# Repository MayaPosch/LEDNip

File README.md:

# LED'Nip #

 LED'Nip is a 5-channel Cortex-M4-based LED controller and general STM32 development board. It has the following features:

- STM32F427 microcontroller (Cortex-M4, 180 MHz).
- 100 MBit Ethernet (LAN8472A).
- CAN (RJ-45 jacks).
- Three 12V channels for RGB LED strips or similar.
- Two channels for ~25 Watt LED panels each (5.5/2.1 mm jack) with constant current regulator (1A LDD-1000H or equivalent per channel).
- 24 VDC board supply voltage.
- SPI, I2C, U(S)ART, I2S and JTAG broken out into JST PH headers.

## Status ##

The LED'Nip hardware has been mostly validated. Test firmware can be found in its folder, with the firmware and backend service that will allow for the board to be used with building lighting and similar still under development.

## Project page

A project & product page can be found at: [http://www.nyantronics.com/lednip.php](http://www.nyantronics.com/lednip.php "LED'Nip")

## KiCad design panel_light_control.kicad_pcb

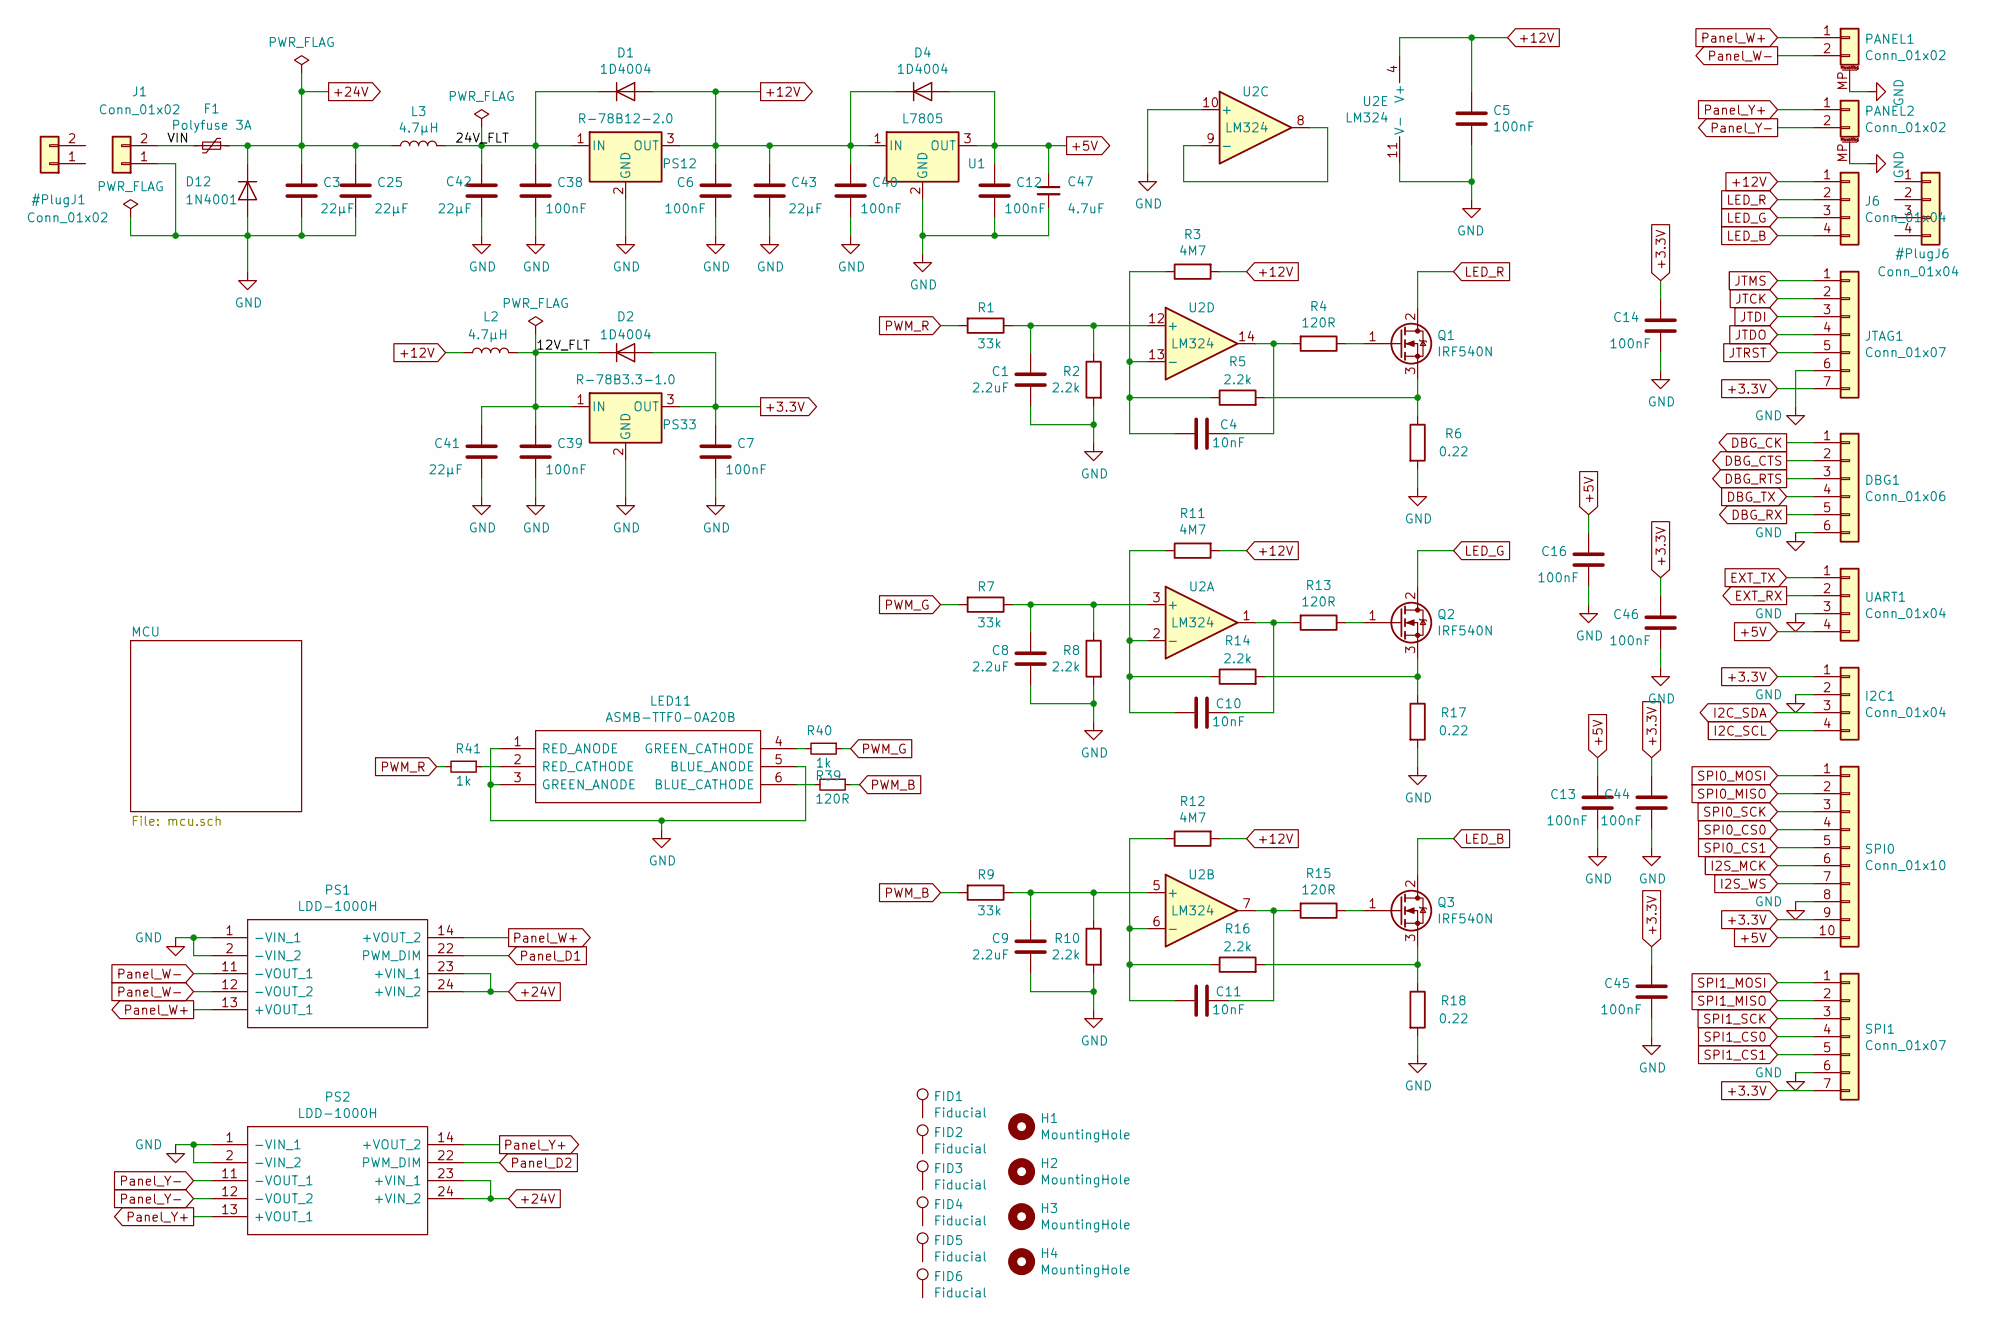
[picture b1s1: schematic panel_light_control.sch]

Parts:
C1, C8, C9: 2.2uF; C_0603_1608Metric; MPN C0603C225K9RACTU; Mouser 80-C0603C225K9R
C3, C25, C41, C42, C43: 22µF; C_1210_3225Metric; MPN GMK325BJ226MM-P; Mouser 963-GMK325BJ226MM-P
C4, C10, C11: 10nF; C_0603_1608Metric; MPN C0603C103K1REAUTO; Mouser 80-C0603C103K1REAUTO
C5, C6, C7, C12, C13, C14, C16, C38, C39, C40, C44, C45, C46: 100nF; C_0603_1608Metric; MPN C0603C104K5RECAUTO; Mouser 80-C0603C104K5REAUTO
C47: 4.7uF; C_0805_2012Metric; MPN GRM21BR71A475KE51L; Mouser 81-GRM21BR71A475KE1L
D1, D2, D4: 1D4004; D_SMA; MPN CGRA4004-G; Mouser 750-CGRA4004-G
D12: 1N4001; D_DO-41_SOD81_P3.81mm_Vertical_AnodeUp; MPN 1N4004-T; Mouser 621-1N4004
DBG1: Conn_01x06; JST_PH_S6B-PH-K_1x06_P2.00mm_Horizontal; MPN S6B-PH-K-S(LF)(SN)‎; DigiKey 455-1723-ND‎
F1: Polyfuse 3A; 30R400UF; MPN 30R300UU; Mouser 576-30R300UU
FID1, FID2, FID3, FID4, FID5, FID6: Fiducial; Fiducial_1mm_Dia_2.54mm_Outer_CopperTop
H1, H2, H3, H4: MountingHole; MountingHole_3.2mm_M3_DIN965
I2C1: Conn_01x04; JST_PH_S4B-PH-K_1x04_P2.00mm_Horizontal; MPN S4B-PH-K-S(LF)(SN)‎; DigiKey 455-1721-ND‎
J1: Conn_01x02; TerminalBlock_Phoenix_MKDS-1,5-2_1x02_P5.00mm_Horizontal; MPN 31320102; Mouser 571-796644-2
J6: Conn_01x04; TerminalBlock_Phoenix_MKDS-1,5-4_1x04_P5.00mm_Horizontal; MPN 31320104
JTAG1: Conn_01x07; JST_PH_S7B-PH-K_1x07_P2.00mm_Horizontal; MPN S7B-PH-K-S(LF)(SN)‎; DigiKey 455-1724-ND‎
L2, L3: 4.7µH; L_Taiyo-Yuden_NR-50xx; MPN VLS5045EX-4R7M-CA; Mouser 810-VLS5045EX4R7MCA
LED11: ASMB-TTF0-0A20B; ASMBTTF00A20B; Manufacturer_Part_Number ASMB-TTF0-0A20B; Mouser Part Number 630-ASMB-TTF0-0A20B
PANEL1, PANEL2: Conn_01x02; BarrelJack_CUI_PJ-063AH_Horizontal; MPN PJ-063AH; Mouser 490-PJ-063AH
PS1, PS2: LDD-1000H; LDD-700H; Manufacturer_Part_Number LDD-1000H; Mouser 709-LDD-1000H
PS12: R-78B12-2.0; Converter_DCDC_RECOM_R-78B-2.0_THT; Manufacturer_Part_Number R-78B12-2.0; Mouser 919-R-78B12-2.0
PS33: R-78B3.3-1.0; Converter_DCDC_RECOM_R-78B-2.0_THT; MPN R-78B3.3-1.0; Mouser 919-R-78B3.3-1.0
Q1, Q2, Q3: IRF540N; TO-220-3_Vertical; MPN IRF540NPBF; Mouser 942-IRF540NPBF
R1, R7, R9: 33k; R_0603_1608Metric; MPN RC0603FR-0733KL; Mouser 603-RC0603FR-0733KL
R2, R5, R8, R10, R14, R16: 2.2k; R_0603_1608Metric; MPN RC0603FR-072K2L; Mouser 603-RC0603FR-072K2L
R3, R11, R12: 4M7; R_0603_1608Metric; MPN RC0603FR-074M7L; Mouser 603-RC0603FR-074M7L
R4, R13, R15, R39: 120R; R_0603_1608Metric; MPN RC0603FR-07120RL; Mouser 603-RC0603FR-07120RL
R6, R17, R18: 0.22; R_1206_3216Metric; MPN KRL1632E-M-R220-F-T5; Mouser 754-KRL1632EMR220FT5
R40, R41: 1k; R_0603_1608Metric; MPN RC0603FR-071KL; Mouser 603-RC0603FR-071KL
SPI0: Conn_01x10; JST_PH_S10B-PH-K_1x10_P2.00mm_Horizontal; MPN S10B-PH-K-S(LF)(SN)‎; DigiKey 455-1727-ND‎
SPI1: Conn_01x07; JST_PH_S7B-PH-K_1x07_P2.00mm_Horizontal; MPN S7B-PH-K-S(LF)(SN); DigiKey 455-1724-ND‎
U1: L7805; TO-220-3_Vertical; MPN L7805CV; Mouser 511-L7805CV
U2: LM324; SOIC-14_3.9x8.7mm_P1.27mm; MPN LM324ADR; Mouser 595-LM324ADR
UART1: Conn_01x04; JST_PH_S4B-PH-K_1x04_P2.00mm_Horizontal; MPN S4B-PH-K-S(LF)(SN)‎; DigiKey 455-1721-ND‎

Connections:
+3.3V: C7.1, C14.1, C44.1, C45.1, C46.1, D2.2 (A), I2C1.1, JTAG1.7, PS33.3 (OUT), SPI0.9, SPI1.7; also elsewhere on the board
+5V: C12.1, C13.1, C16.1, C47.1, D4.2 (A), SPI0.10, U1.3 (OUT), UART1.4; also elsewhere on the board
+12V: C5.2, C6.1, C40.1, C43.1, D1.2 (A), D4.1 (K), J6.1, L2.1, PS12.3 (OUT), R3.2, R11.2, R12.2, U1.1 (IN), U2.4 (V+)
+24V: C3.1, C25.1, D12.1 (K), F1.1, L3.1, PS1.23 (+VIN_1), PS1.24 (+VIN_2), PS2.23 (+VIN_1), PS2.24 (+VIN_2)
/12V_FLT: C39.1, C41.1, D2.1 (K), L2.2, PS33.1 (IN)
/24V_FLT: C38.1, C42.1, D1.1 (K), L3.2, PS12.1 (IN)
/VIN: F1.2, J1.2
DBG_CK: DBG1.1; also elsewhere on the board
DBG_CTS: DBG1.2; also elsewhere on the board
DBG_RTS: DBG1.3; also elsewhere on the board
DBG_RX: DBG1.5; also elsewhere on the board
DBG_TX: DBG1.4; also elsewhere on the board
EXT_RX: UART1.2; also elsewhere on the board
EXT_TX: UART1.1; also elsewhere on the board
GND: C1.1, C3.2, C5.1, C6.2, C7.2, C8.1, C9.1, C12.2, C13.2, C14.2, C16.2, C25.2, C38.2, C39.2, C40.2, C41.2, C42.2, C43.2, C44.2, C45.2, C46.2, C47.2, D12.2 (A), DBG1.6, I2C1.2, J1.1, JTAG1.6, LED11.1 (RED_ANODE), LED11.3 (GREEN_ANODE), LED11.5 (BLUE_ANODE), PANEL1.MP (MountPin), PANEL2.MP (MountPin), PS1.1 (-VIN_1), PS1.2 (-VIN_2), PS2.1 (-VIN_1), PS2.2 (-VIN_2), PS12.2 (GND), PS33.2 (GND), R2.2, R6.2, R8.2, R10.2, R17.2, R18.2, SPI0.8, SPI1.6, U1.2 (GND), U2.10 (+), U2.11 (V-), UART1.3; also elsewhere on the board
I2C_SCL: I2C1.4; also elsewhere on the board
I2C_SDA: I2C1.3; also elsewhere on the board
I2S_MCK: SPI0.6; also elsewhere on the board
I2S_WS: SPI0.7; also elsewhere on the board
JTCK: JTAG1.2; also elsewhere on the board
JTDI: JTAG1.3; also elsewhere on the board
JTDO: JTAG1.4; also elsewhere on the board
JTMS: JTAG1.1; also elsewhere on the board
JTRST: JTAG1.5; also elsewhere on the board
LED_B: J6.4, Q3.2 (D)
LED_G: J6.3, Q2.2 (D)
LED_R: J6.2, Q1.2 (D)
unnamed: C1.2, R1.1, R2.1, U2.12 (+)
unnamed: C4.1, R4.2, U2.14
unnamed: C4.2, R3.1, R5.1, U2.13 (-)
unnamed: C8.2, R7.1, R8.1, U2.3 (+)
unnamed: C9.2, R9.1, R10.1, U2.5 (+)
unnamed: C10.1, R13.2, U2.1
unnamed: C10.2, R11.1, R14.1, U2.2 (-)
unnamed: C11.1, R15.2, U2.7
unnamed: C11.2, R12.1, R16.1, U2.6 (-)
unnamed: LED11.2 (RED_CATHODE), R41.1
unnamed: LED11.4 (GREEN_CATHODE), R40.2
unnamed: LED11.6 (BLUE_CATHODE), R39.2
unnamed: Q1.1 (G), R4.1
unnamed: Q1.3 (S), R5.2, R6.1
unnamed: Q2.1 (G), R13.1
unnamed: Q2.3 (S), R14.2, R17.1
unnamed: Q3.1 (G), R15.1
unnamed: Q3.3 (S), R16.2, R18.1
unnamed: U2.8, U2.9 (-)
PWM_B: R9.2, R39.1; also elsewhere on the board
PWM_G: R7.2, R40.1; also elsewhere on the board
PWM_R: R1.2, R41.2; also elsewhere on the board
Panel_D1: PS1.22 (PWM_DIM); also elsewhere on the board
Panel_D2: PS2.22 (PWM_DIM); also elsewhere on the board
Panel_W+: PANEL1.1, PS1.13 (+VOUT_1), PS1.14 (+VOUT_2)
Panel_W-: PANEL1.2, PS1.11 (-VOUT_1), PS1.12 (-VOUT_2)
Panel_Y+: PANEL2.1, PS2.13 (+VOUT_1), PS2.14 (+VOUT_2)
Panel_Y-: PANEL2.2, PS2.11 (-VOUT_1), PS2.12 (-VOUT_2)
SPI0_CS0: SPI0.4; also elsewhere on the board
SPI0_CS1: SPI0.5; also elsewhere on the board
SPI0_MISO: SPI0.2; also elsewhere on the board
SPI0_MOSI: SPI0.1; also elsewhere on the board
SPI0_SCK: SPI0.3; also elsewhere on the board
SPI1_CS0: SPI1.4; also elsewhere on the board
SPI1_CS1: SPI1.5; also elsewhere on the board
SPI1_MISO: SPI1.2; also elsewhere on the board
SPI1_MOSI: SPI1.1; also elsewhere on the board
SPI1_SCK: SPI1.3; also elsewhere on the board

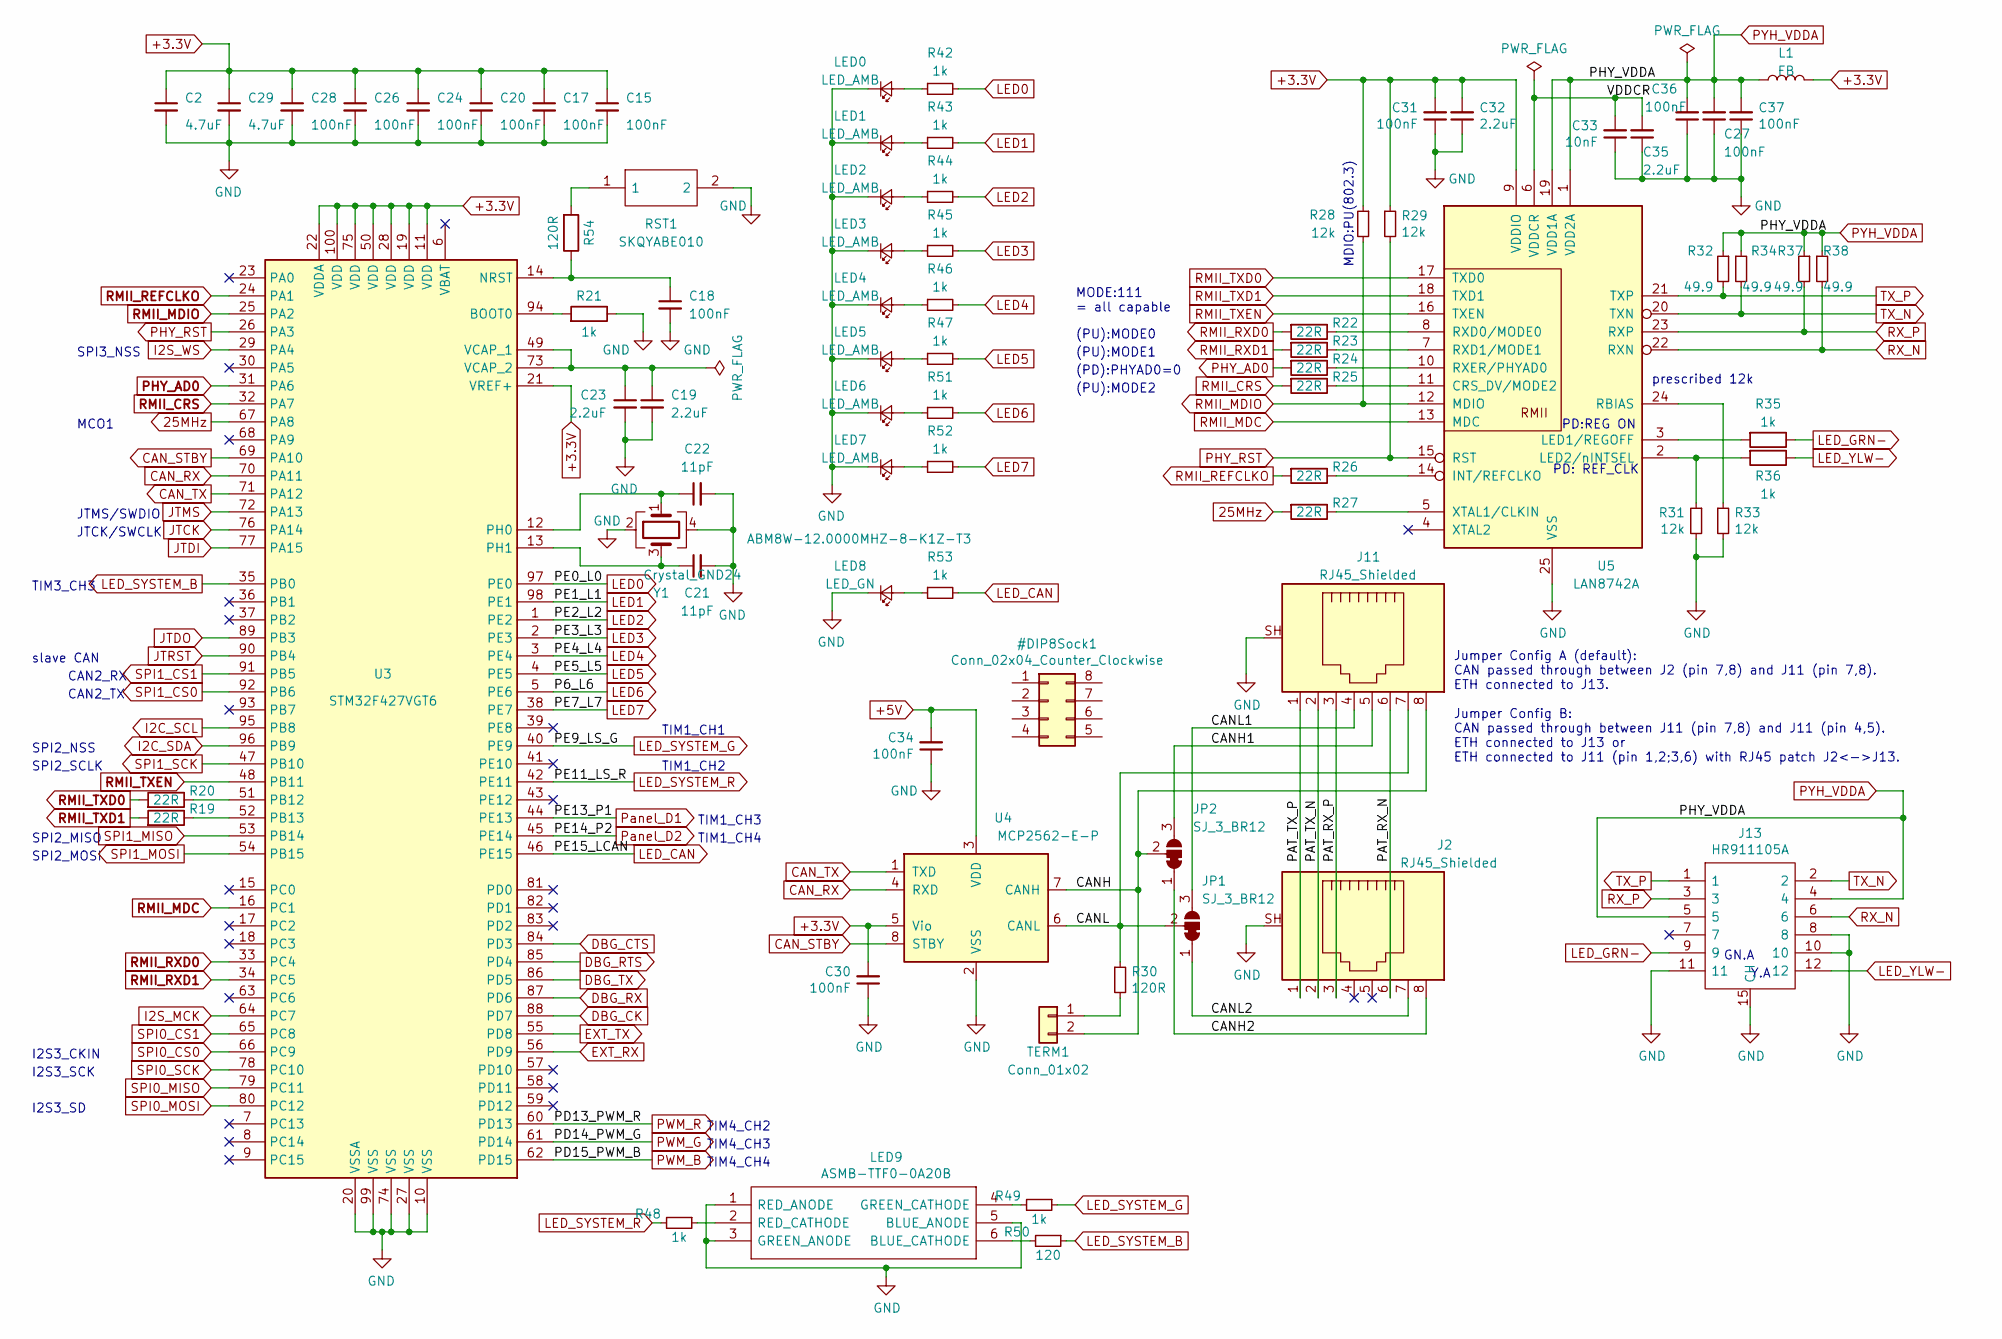
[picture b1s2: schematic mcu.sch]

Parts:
C2, C29: 4.7uF; C_0805_2012Metric; MPN GRM21BR71A475KE51L; Mouser 81-GRM21BR71A475KE1L
C15, C17, C18, C20, C24, C26, C27, C28, C30, C31, C34, C36, C37: 100nF; C_0603_1608Metric; MPN C0603C104K5RECAUTO; Mouser 80-C0603C104K5REAUTO
C19, C23, C32, C35: 2.2uF; C_0603_1608Metric; MPN C0603C225K9RACTU; Mouser 80-C0603C225K9R
C21, C22: 11pF; C_0603_1608Metric; MPN CBR06C110F5GAC; Mouser 80-CBR06C110F5G
C33: 10nF; C_0603_1608Metric; MPN C0603C103K1REAUTO; Mouser 80-C0603C103K1REAUTO
J2, J11: RJ45_Shielded; RJ45_Amphenol_RJHSE5380; MPN RJHSE-5380; Mouser 523-RJHSE-5380
J13: HR911105A; HR911105A_1; Manufacturer_Part_Number HR911105A; Mouser 710-7499011121A (WE near match)
JP1, JP2: SJ_3_BR12; SolderJumper-3_P1.3mm_Bridged12_RoundedPad1.0x1.5mm
L1: FB; L_0603_1608Metric; MPN BLM18KG121TN1D; Mouser 81-BLM18KG121TN1D
LED0, LED1, LED2, LED3, LED4, LED5, LED6, LED7: LED_AMB; LED_0603_1608Metric_Castellated; MPN LTST-C190AKT; Mouser 859-LTST-C190AKT
LED8: LED_GN; LED_0603_1608Metric_Castellated; MPN LTST-C190KGKT; Mouser 859-LTST-C190KGKT
LED9: ASMB-TTF0-0A20B; ASMBTTF00A20B; Manufacturer_Part_Number ASMB-TTF0-0A20B; Mouser Part Number 630-ASMB-TTF0-0A20B
R19, R20, R22, R23, R24, R25, R26, R27: 22R; R_0603_1608Metric; MPN RC0603JR-0722RL; Mouser 603-RC0603JR-0722RL
R21, R35, R36, R42, R43, R44, R45, R46, R47, R49, R51, R52, R53: 1k; R_0603_1608Metric; MPN RC0603FR-071KL; Mouser 603-RC0603FR-071KL
R28, R29, R31, R33: 12k; R_0603_1608Metric; MPN RC0603FR-0712KL; Mouser 603-RC0603FR-0712KL
R30, R54: 120R; R_0603_1608Metric; MPN RC0603FR-07120RL; Mouser 603-RC0603FR-07120RL
R32, R34, R37, R38: 49.9; R_0603_1608Metric; MPN RC0603FR-0749R9L; Mouser 603-RC0603FR-0749R9L
R48: 1k; R_0603_1608Metric; MPN RC0603FR-07120RL; Mouser 603-RC0603FR-07120RL
R50: 120; R_0603_1608Metric; MPN RC0603FR-071KL; Mouser 603-RC0603FR-071KL
RST1: SKQYABE010; Manufacturer_Part_Number SKQYABE010; Mouser 688-SKQYAB
TERM1: Conn_01x02; PinHeader_1x02_P2.54mm_Vertical; MPN S2B-PH-K-S(LF)(SN)‎; DigiKey 455-1719-ND
U3: STM32F427VGT6; LQFP-100_14x14mm_P0.5mm; MPN STM32F427VGT6; Mouser 511-STM32F427VGT6
U4: MCP2562-E-P; DIP-8_W7.62mm_Socket; MPN MCP2562-E/P; Mouser 579-MCP2562-E/P
U5: LAN8742A; QFN-24-1EP_4x4mm_P0.5mm_EP2.6x2.6mm; MPN LAN8742A-CZ-TR; Mouser 579-LAN8742A-CZ-TR
Y1: Crystal_GND24; Crystal_SMD_Abracon_ABM8G-4Pin_3.2x2.5mm; MPN ABM8W-12.0000MHZ-8-K1Z-T3; Mouser 815-8W12-8K1ZT

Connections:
25MHz: R27.2, U3.67 (PA8)
+3.3V: C2.1, C15.1, C17.1, C20.1, C24.1, C26.1, C28.1, C29.1, C30.2, C31.2, C32.2, L1.2, R28.1, R29.1, U3.11 (VDD), U3.19 (VDD), U3.21 (VREF+), U3.22 (VDDA), U3.28 (VDD), U3.50 (VDD), U3.75 (VDD), U3.100 (VDD), U4.5 (Vio), U5.9 (VDDIO); also elsewhere on the board
+5V: C34.2, U4.3 (VDD); also elsewhere on the board
/MCU/CANH: J11.8, JP2.2 (C), TERM1.2, U4.7 (CANH)
/MCU/CANH1: J11.5, JP2.3 (B)
/MCU/CANH2: J2.8, JP2.1 (A)
/MCU/CANL: J11.7, JP1.2 (C), R30.1, U4.6 (CANL)
/MCU/CANL1: J11.4, JP1.3 (B)
/MCU/CANL2: J2.7, JP1.1 (A)
/MCU/PAT_RX_N: J2.6, J11.6
/MCU/PAT_RX_P: J2.3, J11.3
/MCU/PAT_TX_N: J2.2, J11.2
/MCU/PAT_TX_P: J2.1, J11.1
/MCU/VDDCR: C33.2, C35.2, U5.6 (VDDCR)
CAN_RX: U3.70 (PA11), U4.4 (RXD)
CAN_STBY: U3.69 (PA10), U4.8 (STBY)
CAN_TX: U3.71 (PA12), U4.1 (TXD)
DBG_CK: U3.88 (PD7); also elsewhere on the board
DBG_CTS: U3.84 (PD3); also elsewhere on the board
DBG_RTS: U3.85 (PD4); also elsewhere on the board
DBG_RX: U3.87 (PD6); also elsewhere on the board
DBG_TX: U3.86 (PD5); also elsewhere on the board
EXT_RX: U3.56 (PD9); also elsewhere on the board
EXT_TX: U3.55 (PD8); also elsewhere on the board
GND: C2.2, C15.2, C17.2, C18.2, C19.2, C20.2, C21.2, C22.2, C23.2, C24.2, C26.2, C27.1, C28.2, C29.2, C30.1, C31.1, C32.1, C33.1, C34.1, C35.1, C36.1, C37.1, J2.SH, J11.SH, J13.8, J13.10, J13.11, J13.15 (CH), J13.16 (CH), LED0.1 (K), LED1.1 (K), LED2.1 (K), LED3.1 (K), LED4.1 (K), LED5.1 (K), LED6.1 (K), LED7.1 (K), LED8.1 (K), LED9.1 (RED_ANODE), LED9.3 (GREEN_ANODE), LED9.5 (BLUE_ANODE), R21.1, R31.2, R33.2, RST1.2, U3.10 (VSS), U3.20 (VSSA), U3.27 (VSS), U3.74 (VSS), U3.99 (VSS), U4.2 (VSS), U5.25 (VSS), Y1.2, Y1.4; also elsewhere on the board
I2C_SCL: U3.95 (PB8); also elsewhere on the board
I2C_SDA: U3.96 (PB9); also elsewhere on the board
I2S_MCK: U3.64 (PC7); also elsewhere on the board
I2S_WS: U3.29 (PA4); also elsewhere on the board
JTCK: U3.76 (PA14); also elsewhere on the board
JTDI: U3.77 (PA15); also elsewhere on the board
JTDO: U3.89 (PB3); also elsewhere on the board
JTMS: U3.72 (PA13); also elsewhere on the board
JTRST: U3.90 (PB4); also elsewhere on the board
LED0: R42.2, U3.97 (PE0)
LED1: R43.2, U3.98 (PE1)
LED2: R44.2, U3.1 (PE2)
LED3: R45.2, U3.2 (PE3)
LED4: R46.2, U3.3 (PE4)
LED5: R47.2, U3.4 (PE5)
LED6: R51.2, U3.5 (PE6)
LED7: R52.2, U3.38 (PE7)
LED_CAN: R53.2, U3.46 (PE15)
LED_GRN-: J13.9, R35.1
LED_SYSTEM_B: R50.1, U3.35 (PB0)
LED_SYSTEM_G: R49.1, U3.40 (PE9)
LED_SYSTEM_R: R48.2, U3.42 (PE11)
LED_YLW-: J13.12, R36.1
unnamed: C18.1, R54.1, U3.14 (NRST)
unnamed: C19.1, C23.1, U3.49 (VCAP_1), U3.73 (VCAP_2)
unnamed: C21.1, U3.13 (PH1), Y1.3
unnamed: C22.1, U3.12 (PH0), Y1.1
unnamed: LED0.2 (A), R42.1
unnamed: LED1.2 (A), R43.1
unnamed: LED2.2 (A), R44.1
unnamed: LED3.2 (A), R45.1
unnamed: LED4.2 (A), R46.1
unnamed: LED5.2 (A), R47.1
unnamed: LED6.2 (A), R51.1
unnamed: LED7.2 (A), R52.1
unnamed: LED8.2 (A), R53.1
unnamed: LED9.2 (RED_CATHODE), R48.1
unnamed: LED9.4 (GREEN_CATHODE), R49.2
unnamed: LED9.6 (BLUE_CATHODE), R50.2
unnamed: R19.1, U3.52 (PB13)
unnamed: R20.1, U3.51 (PB12)
unnamed: R21.2, U3.94 (BOOT0)
unnamed: R22.1, U5.8 (RXD0/MODE0)
unnamed: R23.1, U5.7 (RXD1/MODE1)
unnamed: R24.1, U5.10 (RXER/PHYAD0)
unnamed: R25.1, U5.11 (CRS_DV/MODE2)
unnamed: R26.1, U5.14 (INT/REFCLKO)
unnamed: R27.1, U5.5 (XTAL1/CLKIN)
unnamed: R30.2, TERM1.1
unnamed: R31.1, R36.2, U5.2 (LED2/nINTSEL)
unnamed: R33.1, U5.24 (RBIAS)
unnamed: R35.2, U5.3 (LED1/REGOFF)
unnamed: R54.2, RST1.1
PHY_AD0: R24.2, U3.31 (PA6)
PHY_RST: R29.2, U3.26 (PA3), U5.15 (RST)
PWM_B: U3.62 (PD15); also elsewhere on the board
PWM_G: U3.61 (PD14); also elsewhere on the board
PWM_R: U3.60 (PD13); also elsewhere on the board
PYH_VDDA: C27.2, C36.2, C37.2, J13.4, J13.5, L1.1, R32.1, R34.1, R37.1, R38.1, U5.1 (VDD2A), U5.19 (VDD1A)
Panel_D1: U3.44 (PE13); also elsewhere on the board
Panel_D2: U3.45 (PE14); also elsewhere on the board
RMII_CRS: R25.2, U3.32 (PA7)
RMII_MDC: U3.16 (PC1), U5.13 (MDC)
RMII_MDIO: R28.2, U3.25 (PA2), U5.12 (MDIO)
RMII_REFCLKO: R26.2, U3.24 (PA1)
RMII_RXD0: R22.2, U3.33 (PC4)
RMII_RXD1: R23.2, U3.34 (PC5)
RMII_TXD0: R20.2, U5.17 (TXD0)
RMII_TXD1: R19.2, U5.18 (TXD1)
RMII_TXEN: U3.48 (PB11), U5.16 (TXEN)
RX_N: J13.6, R38.2, U5.22 (RXN)
RX_P: J13.3, R37.2, U5.23 (RXP)
SPI0_CS0: U3.66 (PC9); also elsewhere on the board
SPI0_CS1: U3.65 (PC8); also elsewhere on the board
SPI0_MISO: U3.79 (PC11); also elsewhere on the board
SPI0_MOSI: U3.80 (PC12); also elsewhere on the board
SPI0_SCK: U3.78 (PC10); also elsewhere on the board
SPI1_CS0: U3.92 (PB6); also elsewhere on the board
SPI1_CS1: U3.91 (PB5); also elsewhere on the board
SPI1_MISO: U3.53 (PB14); also elsewhere on the board
SPI1_MOSI: U3.54 (PB15); also elsewhere on the board
SPI1_SCK: U3.47 (PB10); also elsewhere on the board
TX_N: J13.2, R34.2, U5.20 (TXN)
TX_P: J13.1, R32.2, U5.21 (TXP)

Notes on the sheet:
MCO1
prescribed 12k
PD:REG ON
PD: REF_CLK
MDIO:PU(802.3)
(PU):MODE0
(PU):MODE1
(PU):MODE2
(PD):PHYAD0=0
MODE:111 = all capable
GN.A
Y.A
JTMS/SWDIO
JTCK/SWCLK
CAN2_RX
CAN2_TX
slave CAN
I2S3_SD
I2S3_SCK
I2S3_CKIN
SPI3_NSS
SPI2_SCLK
SPI2_MOSI
SPI2_MISO
SPI2_NSS
TIM1_CH3
TIM1_CH4
TIM4_CH2
TIM4_CH3
TIM4_CH4
TIM3_CH3
TIM1_CH1
TIM1_CH2
Jumper Config A (default): CAN passed through between J2 (pin 7,8) and J11 (pin 7,8). ETH connected to J13. Jumper Config B: CAN passed through between J11 (pin 7,8) and J11 (pin 4,5). ETH connected to J13 or ETH connected to J11 (pin 1,2;3,6) with RJ45 patch J2<->J13.

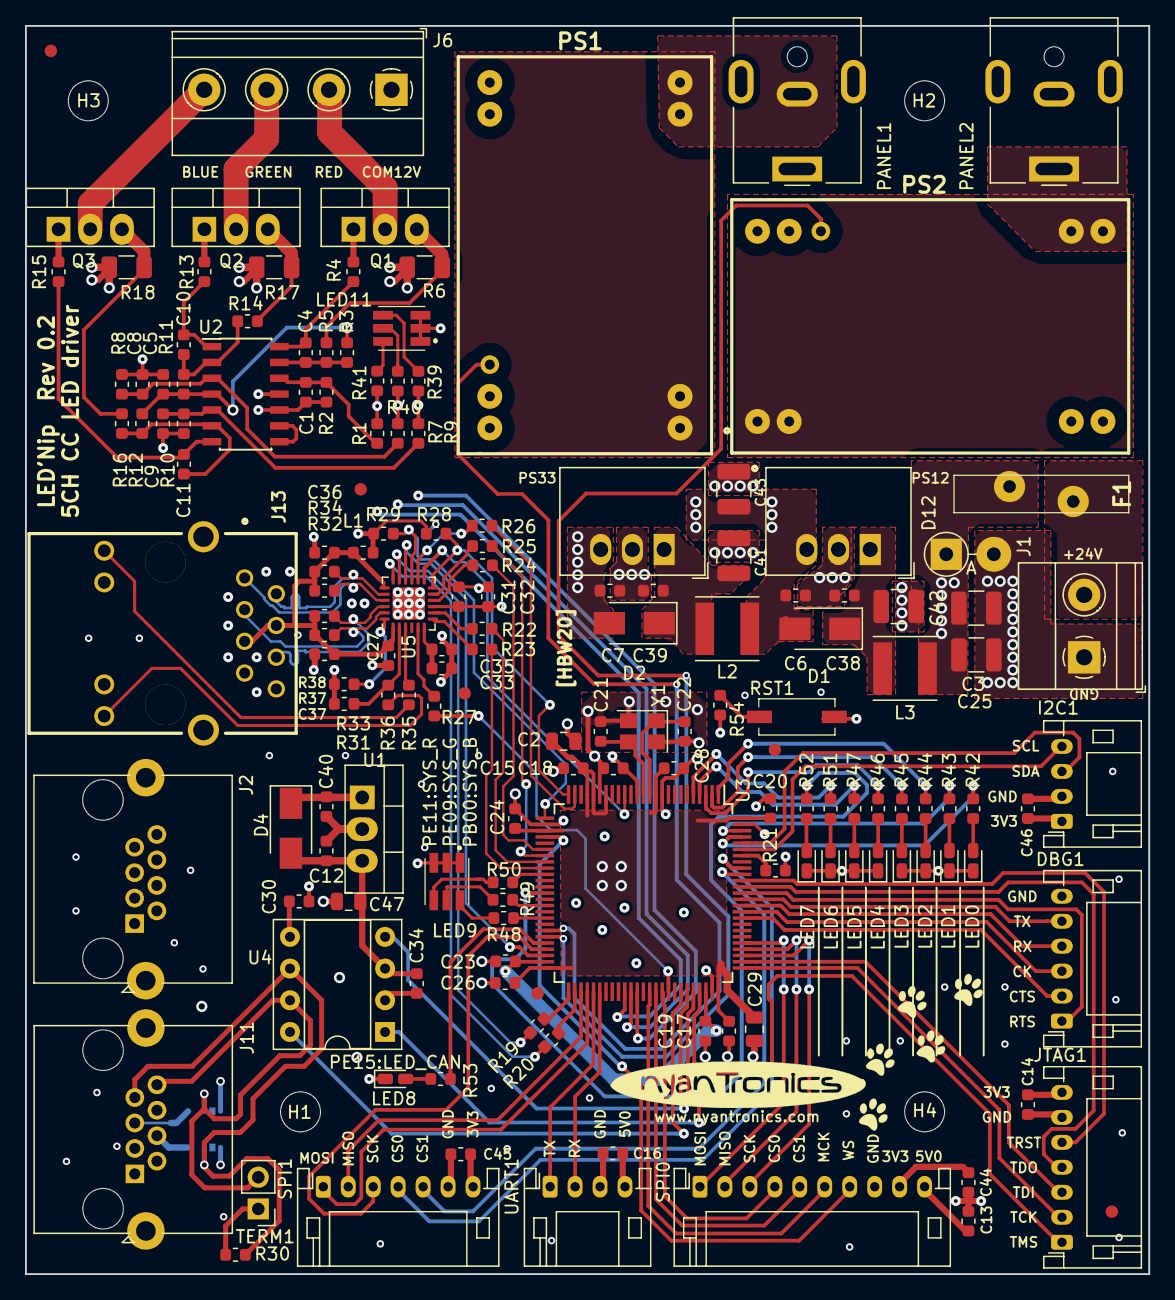
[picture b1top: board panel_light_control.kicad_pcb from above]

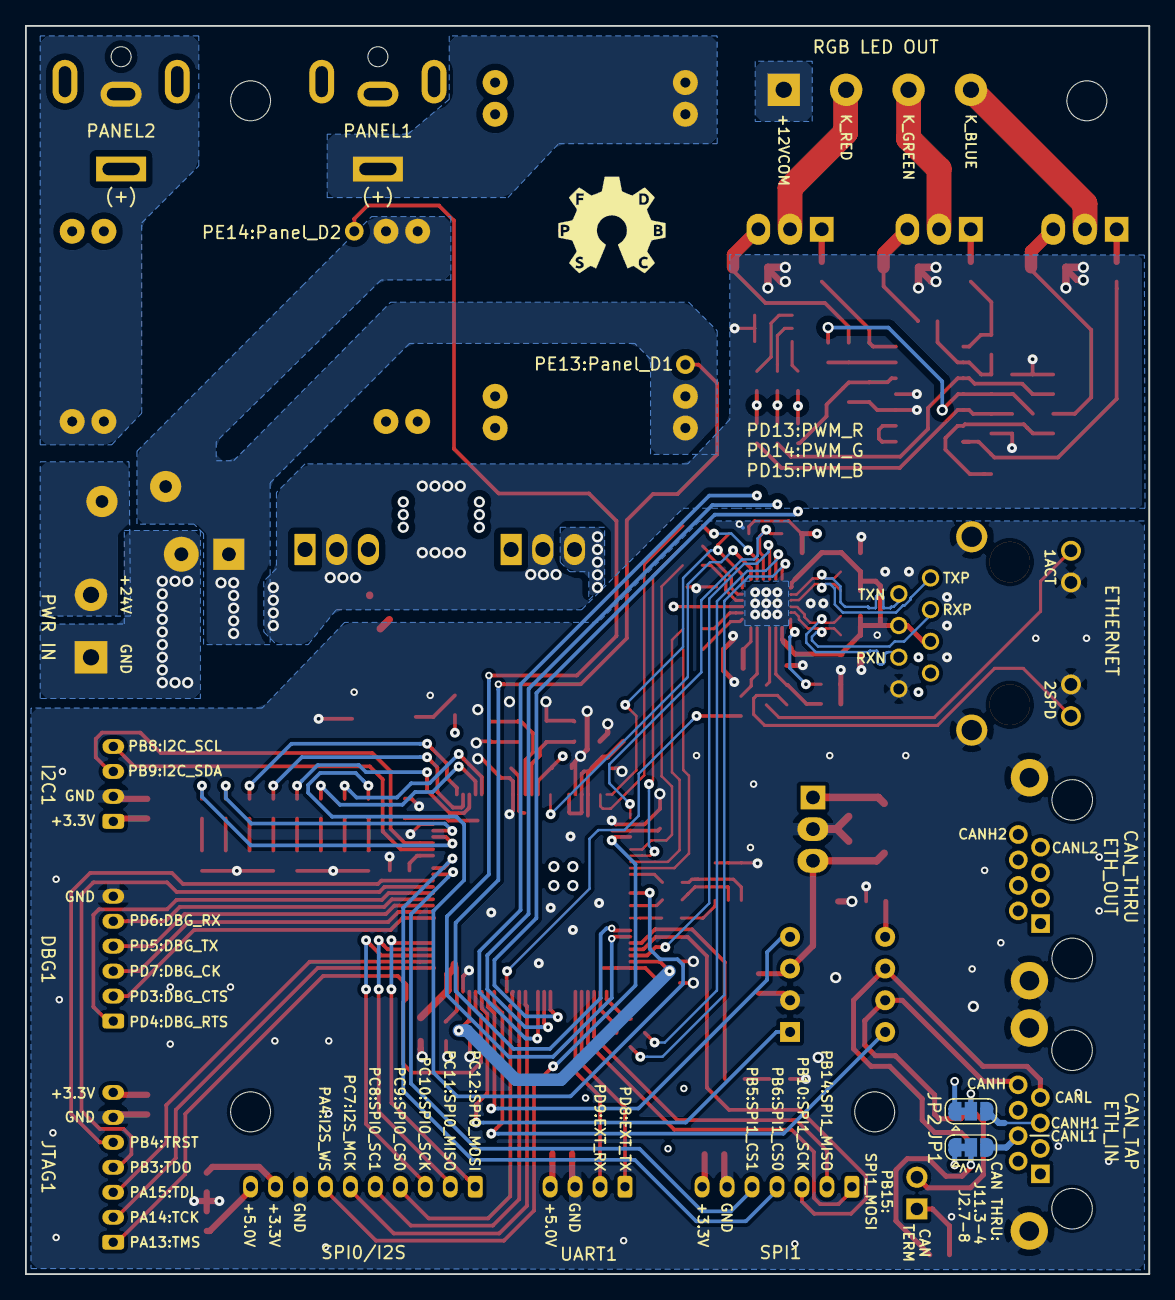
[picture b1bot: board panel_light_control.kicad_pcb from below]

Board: 4 copper layers, 90.0 x 100.0 mm, 160 parts (2 on the bottom side), 140 nets.

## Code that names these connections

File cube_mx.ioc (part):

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Mcu.Name=STM32F207V(C-E-F-G)Tx
Mcu.Package=LQFP100
Mcu.UserName=STM32F207VGTx
PA1.Mode=RMII
PA1.Signal=ETH_REF_CLK
PA10.GPIOParameters=GPIO_Label
PA10.GPIO_Label=CAN_STBY
PA10.Signal=GPIO_Output
PA11.Mode=Master
PA11.Signal=CAN1_RX
PA12.Mode=Master
PA12.Signal=CAN1_TX
PA13.Mode=JTAG_5_pins
PA13.Signal=SYS_JTMS-SWDIO
PA14.Mode=JTAG_5_pins
PA14.Signal=SYS_JTCK-SWCLK
PA15.Mode=JTAG_5_pins
PA15.Signal=SYS_JTDI
PA2.Mode=RMII
PA2.Signal=ETH_MDIO
PA3.GPIOParameters=GPIO_Label
PA3.GPIO_Label=PHY_RST
PA3.Signal=GPIO_Output
PA4.Mode=NSS_Signal_Hard_Output
PA4.Signal=SPI3_NSS
PA6.GPIOParameters=GPIO_Label
PA6.GPIO_Label=PHY_AD0
PA6.Signal=GPIO_Output
PA7.Mode=RMII
PA7.Signal=ETH_CRS_DV
PA8.Mode=Clock-out-1
PA8.Signal=RCC_MCO_1
PB0.GPIOParameters=GPIO_Label
PB0.GPIO_Label=LED_SYSTEM_B
PB0.Signal=S_TIM3_CH3
PB10.Mode=Full_Duplex_Master
PB10.Signal=SPI2_SCK
PB11.Mode=RMII
PB11.Signal=ETH_TX_EN
PB12.Mode=RMII
PB12.Signal=ETH_TXD0
PB13.Mode=RMII
PB13.Signal=ETH_TXD1
PB14.Mode=Full_Duplex_Master
PB14.Signal=SPI2_MISO
PB15.Mode=Full_Duplex_Master
PB15.Signal=SPI2_MOSI
PB3.Mode=JTAG_5_pins
PB3.Signal=SYS_JTDO-SWO
PB4.Mode=JTAG_5_pins
PB4.Signal=SYS_JTRST
PB5.GPIOParameters=GPIO_Label
PB5.GPIO_Label=SPI2_CS1
PB5.Signal=GPIO_Output
PB6.GPIOParameters=GPIO_Label
PB6.GPIO_Label=SPI2_CS0
PB6.Signal=GPIO_Output
PB8.Mode=I2C
PB8.Signal=I2C1_SCL
PB9.Mode=I2C
PB9.Signal=I2C1_SDA
PC1.Mode=RMII
PC1.Signal=ETH_MDC
PC10.Mode=Full_Duplex_Master
PC10.Signal=SPI3_SCK
PC11.Mode=Full_Duplex_Master
PC11.Signal=SPI3_MISO
PC12.Mode=Full_Duplex_Master
PC12.Signal=SPI3_MOSI
PC4.Mode=RMII
PC4.Signal=ETH_RXD0
PC5.Mode=RMII
PC5.Signal=ETH_RXD1
PC8.GPIOParameters=GPIO_Label
PC8.GPIO_Label=SPI3_CS0
PC8.Signal=GPIO_Output
PC9.GPIOParameters=GPIO_Label
PC9.GPIO_Label=I2S_CKIN/CS1
PC9.Mode=Audio_ClockIn
PC9.Signal=I2S_CKIN
PD13.GPIOParameters=GPIO_Label
PD13.GPIO_Label=PWM_R
PD13.Signal=S_TIM4_CH2
PD14.GPIOParameters=GPIO_Label
PD14.GPIO_Label=PWM_G
PD14.Signal=S_TIM4_CH3
PD15.GPIOParameters=GPIO_Label
PD15.GPIO_Label=PWM_B
PD15.Signal=S_TIM4_CH4
PD3.Mode=CTS_RTS
PD3.Signal=USART2_CTS
PD4.Mode=CTS_RTS
PD4.Signal=USART2_RTS
PD5.Mode=Asynchronous
PD5.Signal=USART2_TX
PD6.Mode=Asynchronous
PD6.Signal=USART2_RX
PD8.Mode=Asynchronous
PD8.Signal=USART3_TX
PD9.Mode=Asynchronous
PD9.Signal=USART3_RX
PE0.GPIOParameters=GPIO_Label
PE0.GPIO_Label=LED0
PE0.Signal=GPIO_Output
PE1.GPIOParameters=GPIO_Label
PE1.GPIO_Label=LED1
PE1.Signal=GPIO_Output
PE11.GPIOParameters=GPIO_Label
PE11.GPIO_Label=LED_SYSTEM_R
PE11.Signal=S_TIM1_CH2
PE13.GPIOParameters=GPIO_Label
PE13.GPIO_Label=PANEL_D1
PE13.Signal=S_TIM1_CH3
PE14.GPIOParameters=GPIO_Label
PE14.GPIO_Label=PANEL_D2
PE14.Signal=S_TIM1_CH4
PE15.GPIOParameters=GPIO_Label
PE15.GPIO_Label=LED_CAN
PE15.Signal=GPIO_Output
PE2.GPIOParameters=GPIO_Label
PE2.GPIO_Label=LED2
PE2.Signal=GPIO_Output
PE3.GPIOParameters=GPIO_Label
PE3.GPIO_Label=LED3
PE3.Signal=GPIO_Output
PE4.GPIOParameters=GPIO_Label
PE4.GPIO_Label=LED4
PE4.Signal=GPIO_Output
PE5.GPIOParameters=GPIO_Label
PE5.GPIO_Label=LED5
PE5.Signal=GPIO_Output
PE6.GPIOParameters=GPIO_Label
PE6.GPIO_Label=LED6
PE6.Signal=GPIO_Output
PE7.GPIOParameters=GPIO_Label
PE7.GPIO_Label=LED7
PE7.Signal=GPIO_Output
PE9.GPIOParameters=GPIO_Label
PE9.GPIO_Label=LED_SYSTEM_G
PE9.Signal=S_TIM1_CH1
PH0-OSC_IN.Mode=HSE-External-Oscillator
PH0-OSC_IN.Signal=RCC_OSC_IN
PH1-OSC_OUT.Mode=HSE-External-Oscillator
PH1-OSC_OUT.Signal=RCC_OSC_OUT
RCC.HSE_VALUE=12000000
RCC.SYSCLKFreq_VALUE=100000000
RCC.SYSCLKSource=RCC_SYSCLKSOURCE_PLLCLK
board=custom

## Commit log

2018-10-14 Initial commit. Finish programming/debug interface.
2018-10-16 Finished initial schematic review.
2018-10-16 Tweak I2S breakout, generate netlist.
2018-10-17 Started layouting.
2018-10-17 Sorted passives on board.
2018-10-17 Finished initial layout LED CV, CAN.
2018-10-17 Finished basic board layout.
2018-10-18 Board layout tweaks.
2018-10-18 Tweaking power section layout.
2018-10-18 Finished initial PHY-magjack routing.
2018-10-20 adds PHY PU/PD config pin comments
2018-10-21 schematic clean-up, BOM info partially added
2018-10-21 PHY routing done? Current sink routing is back to square one (yay fwd annotations)
2018-10-21 further re-arrangement, PCB is now 100x90 mm² \o/. A bit more placement to do, then back to routing :>
2018-10-22 Tweaked LED sink layout, fixed 3D model for 1 RJ45 jack.
2018-10-22 Tweaked MOSFET sink layout. Changed LM324 to SOIC.
2018-10-22 Add LEDs, tweak MOSFET sink.
2018-10-22 3.3V buck converter now connected to 12V (prep for 48V>12V upgrade regarding IoP applicability)
2018-10-22 two sections left to place: 3ch current sink, microcontroller area. Todo: * find proper barrel jacks, spec MPN, Mouser * add status LEDs to the LDD-H outputs * add 7th LED for funsies :> * swap LM324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
2018-10-23 THT pad restring sizes increase for mechanical stability; generalized LED arrangement for more flexibility (8 bit display, CAN LED, PWM and general purpose RGB) and development-style look and feel; p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
2018-10-23 R-78B3.3 footprint fixed (had the E version -> mirrored), next: place remaining current sink circuit parts, route upper half of the PCB, tidy up CAN placement, verify µC pin mapping again, route lowe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
2018-10-27 RGB current sink placed and routed. All placement should be done now, next: check barrel jack footprint, do power routing, think about input protection for GPIOs, possibly add resistor arrays, route 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
2018-10-27 silkscreen clean-up
2018-10-27 PS1-> Panel1, PS2-> Panel2, PS12->12V, PS33-> 3.3V.
2018-10-27 missed silkscreen bits tidied up
2018-10-27 add CAN termination jumper, switch-mode DCDC power routing and current sink routing done. Barrel jacks still need swapping?
2018-10-27 change I2S connector footprint back from 11 pin to 10 pin (MCK, SCK, WS... missing something?). More silkscreen clean-up and a bit of routing.
2018-10-27 minor touch-ups. ToDo: think about barrel jacks, input protection, finish routing (RMII, 3.3V plane and traces, general purpose signals), then review.
2018-10-27 routing almost done. ToDo: fix symbols to include shielding on some connectors. finish routing. Add GND copper pour on bottom side.
2018-10-27 first pass routing done (0 air wires). ToDo: fix connector shielding.
2018-10-28 all connector shields are now connected to ground. Note HR911105A LED pins are offset by 4.9mm whereas the WE LED pins are at 4.1mm. Can still fit the WE part? but it won't be pretty.
2018-10-28 lots of labels!
2018-10-28 Removed redundant silkscreen labels.
2018-10-28 Changes to 3.3V polygon shape to remove overlap with 24V, 12V input section. Some improvements and corrections to the silkscreen. 7805 location checked for 78B05 clearance - will work in case 5V >100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
2018-10-28 Added board art.
2018-10-28 added BOM info, minor tweaks to artwork
2018-11-01 adds reset button, some xtal guarding. Schematic reviewed in this version, see https://hackmd.io/-iUjavK_Rz-11sfgLlTnuA# - xtal could be swapped for C_L 10 pF version to reduce susceptibility to envi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
2018-11-04 pinout validated against CubeMX listing (.ioc added), some nets renamed, system RGB LED reconnected. Reconnected I2C lines to include CAN alternate function. Warning: * bottom silkscreen labels might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
2018-11-05 swap xtal for 12 MHz type with CL=8pF -> 2MHz PLL in (optimum), larger load capacitors offering higher noise immunity, HSE gain margin should still be ok, silk screen changes due to secondary CAN int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
2018-11-05 Generated v0.1 Gerbers & Drill file.
2018-11-05 final touches: add fiducials for PCBA
2018-11-05 Update Gerbers & Drill files.
2018-11-06 add project flow diagram for the deployment of 25+ boards. Get draw.io: https://about.draw.io/integrations/#integrations_offline
2018-11-16 BOM DONE
2018-11-16 BOM completed, inventory checked and listed in BOM. Adds project diagram.
2018-11-25 PLCC-4 RGB LEDs LED9 and LED10 are the wrong parts (common cathode required, part is common anode and different input). Fix: source 0606 LEDs (metric 1616) - RD1616-63RGBC-C2CA or DL-PCB0606RGBC-C2. 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
2018-12-12 project moving forward (draw.io diagram updated), added test report (work in progress)
2019-01-01 Created an OpenOCD config file and documentation on it. Added quick protocol of the hardware power-up.
2019-01-01 Add auto-generated firmware. Modify Makefile to add 'flash' target.
2019-01-01 added -event reset-assert to define system reset (replacing srst), including documentation.
2019-01-02 .cfg comments updated
2019-01-02 channel 1 pins are called BDBUSn, names updated. Verified reset things (signal is called nTRST while the function is called trst... which is a bit odd but seems to be valid. The AIRCR write also seem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
2019-01-02 includes answers to the "-event reset-assert" usage question, adds flashing capability to the makefile. In essence, OpenOCD contains all reset functionality needed for an STM32F4 through config and b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
2019-01-04 Add initial code for interrupt routine for LED demo on TIM2
2019-01-06 Finish PWM curve for panel D1 pin for initial testing.
2019-01-06 Attempt to implement interrupt-based timer for PWM manipulation...
2019-01-06 Get basic dimming working on LED panel output D1.
2019-01-07 change PWM mode from TIM_COUNTERMODE_UP to TIM_COUNTERMODE_CENTERALIGNED1 and change TIM1 CH4 OCPolarity from TIM_OCPOLARITY_HIGH to TIM_OCPOLARITY_LOW to create 180° interleaved PWM within one TIM. 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
2019-01-07 modified init for TIM1, TIM3, TIM4 (up -> centeraligned1, same period, same prescaler). Dedicated update functions for the RGB and panel PWM groups. Runs on hardware but the PWM frequency needs to be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
2019-01-09 Enable basic PWM sweep on RGB LED channels.
2019-01-09 Add rough HSV-based colour sweep on the RGB PWM pins.
2019-01-09 Change PWM limit division factor for 70% max current on RGB outputs.
2019-01-09 Add brief linger at the ends of the RGB PWM sweep sequence.
2019-01-10 Tweak linger on HSV colour sweep begin and end points.
2019-01-10 introduces user constants PWM_TIMER_RELOAD,10000;PWM_TIMER_PRESCALER,12 and properly configures TIM1, TIM3 and TIM4 (all TIM_COUNTERMODE_CENTERALIGNED1, ITM1 ClockDivision set to TIM_CLOCKDIVISION_DI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
2019-01-11 attempt to sort code back into USER labelled sections to be compatible with CubeMX behaviour.
2019-01-12 Updated project according to .ioc file. Experimentation with RELOAD and PRESCALER to debug TIM4 "clock too slow" issue. APB1: 50MHz, APB2: 100MHz. RELOAD = 10000. PRESCALER = 9: 4 ms period, PRESCALE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
2019-01-13 played around with CK_IN prescalers for TIM1 and TIM3..4. APB1 and APB2 timer clocks are both 80 MHz now so TIM1, TIM3 and TIM4 behave consistently. +RCC.48MHZClocksFreq_Value=40000000 +RCC.AHBFreq_V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
2019-01-14 sets PHY_RST from push-pull low to open-drain high to release nRST, PHYAD0 is kept low -> 0x00 changed in CubeMX from 1 to 0. Change SPI CS pins from low to high speed GPIO. Current draw is higher an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
2019-03-10 restored MCO1 = 25 MHz, PHY blinking pattern changed (SPEED on permanently, ACT fast blinking, RMII-RXDn activity) but TXEN only stays high for 6µs max. No SMI activity within 100ms after that.
2019-03-12 restored clock setup (source was int. RC, now back to 12 MHz ext. xtal), MCO verified to be 25.000 MHz. Played around with lwip checksum generation. Also recommend looking at CubeMX stacked pin optio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
2019-03-13 add MX_LWIP_Process(); to main loop (non-interrupt-based polling mode for non-OS operation) ... not added by CubeMX. Why?
2019-03-14 deactivating ETH hardware checksum generation and enabling LWIP software checksum generation makes icmp work, ping. Should be revisited and evaluated in terms for performance hits, but works for now.
2019-05-05 Add README & license.
2019-07-05 Start MVP firmware.
2019-07-06 [MVP] Tested compiling with new STM32 functionality in Nodate framework.
2019-07-06 [MVP] Implement MQTT processing and pin assignment for RGB strips.
2019-07-07 [Firmware] Integrate LWIP MQTT client support for remote LED dimming.
2019-07-07 [MVP] Tweak MVP code. Ethernet interface not working yet.
2019-07-09 Update for v0.2. Revise schematic and PCB layout. See dev log.
2020-03-07 `vallen` is verified to be less than `len`, therefore, it can never be the case that `vallen >= len + sizeof(rhostname)`.
    This PR fixes the check so the `rhostname` array does not overflow.
    Reported-by: Github Security Lab <securitylab@github.com>
2020-04-06 * STM32 pin 99 not connected in layout -> GND * STM32 pin 10 not connected in schematic -> GND * added solder jumpers JP1, JP2 with default bridges to select between new CAN routing options * J2 and 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
